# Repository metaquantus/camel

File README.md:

# Camel I2C Dual HX712 Weigh Scales Board

Camel is a board with Dual HX712 Weigh Scales ADCs controlled by a low power STM32L010F4 or STM32L031F6 MCU providing an I2C slave interface.
Power is provided by an I2C Adafruit STEMMA compatible 4-pin JST PH (2mm pitch) connector. This board will work 
with power from 3.3V to 5V, but it's better if VCC > 4V. 

It was intended to support the integrated scales mod for the Gaggia Classic Pro espresso machine provided by the Gaggiuino project. But instead of the main MCU driving the HX712s directly, sensor reading and decoding is offloaded to this board's MCU and a simple I2C interface is used instead to connect to the host MCU. This reduces the number of wires required, frees some pins in the host MCU and saves some clock cycles.

STEMMA Pinouts:
```
1 Green for SCL
2 White for SDA
3 Red for VCC+
4 Black for GND
```

The MCU drives the 2 HX712 ADCs, reads and decodes the conversions and provides the raw data to the host via I2C. 
The HX712s allow programmatic configuration of the sampling rate (10Hz or 40Hz), the amplifier's gain
factor (128 or 256) and whether to put the HX712s into power down mode consuming less than 1uA.
The device can also store configuration and calibration points in the MCU's EEPROM. Up to 4 calibration points 
are supported. 
The host is in charge of providing additional functions like scaling to weight units, tare and calibration.
It may be possible to offload scaling to the MCU, if using STM32L031F6 as it has more memory.
I2C doesn't support slave initiated transfers so the host MCU must poll the device periodically to read the data.
There will be roughly one new sensor reading available of both load cells every 100ms if 10Hz sampling rate is used. 
The internal oscillator is used in both the HX712 ADCs and the MCU so sampling rates are not very precise.
Using the lower sampling rate has lower conversion noise. The HX712 is a 24-bit ADC and data is provided in 2's complement format.
Readings could be negative depending on how the load cell is mechanically setup, bending one way of the other.
For example, in some of the integrated scales mod assembles, one cell gives positive values and 
the other negative. To get the total weight reading, the absolute values of both cells should be added.

According to STM32CubeIDE, the MCU should consume about 5mA and the HX712s about 1mA each. 

If using only one of the HX712s, it's possible power down the other, saving 1mA. This can be configured from
the host.

Programming is done via a Serial Wire Debug (SWD) connector. Both a Tag-Connect TC2030-NL and a 4-pin 2.54mm pitch header are provided for SWD.

A USART connector is provided but the STM32L010F4 has only 16Kb flash/2Kb RAM and adding code support exceeds code size limit. Some reporting
was tried but code size was very tight. This was intended for monitor and debugging during development, so it's not essential. Maybe with the
STM32L031F6 with 32KB flash/8KB RAM more monitoring and functions like standalone calibration can be added.

ESD protection diodes were added to the interface connectors.

2.54mm pitch header THT pads are used for the load cell connectors, but normally the load cells wires should be soldered directly to the pads instead of using headers or other connector.

## PCB Notes

The variable FAB\_ON\_PLACEHOLDER should be set to JLCJLCJLCJLC, WayWayWay or whatever string is specified by the Fab to position the order number.
Or removed altogether if so desired. Sometimes a fee is incurred if removed.

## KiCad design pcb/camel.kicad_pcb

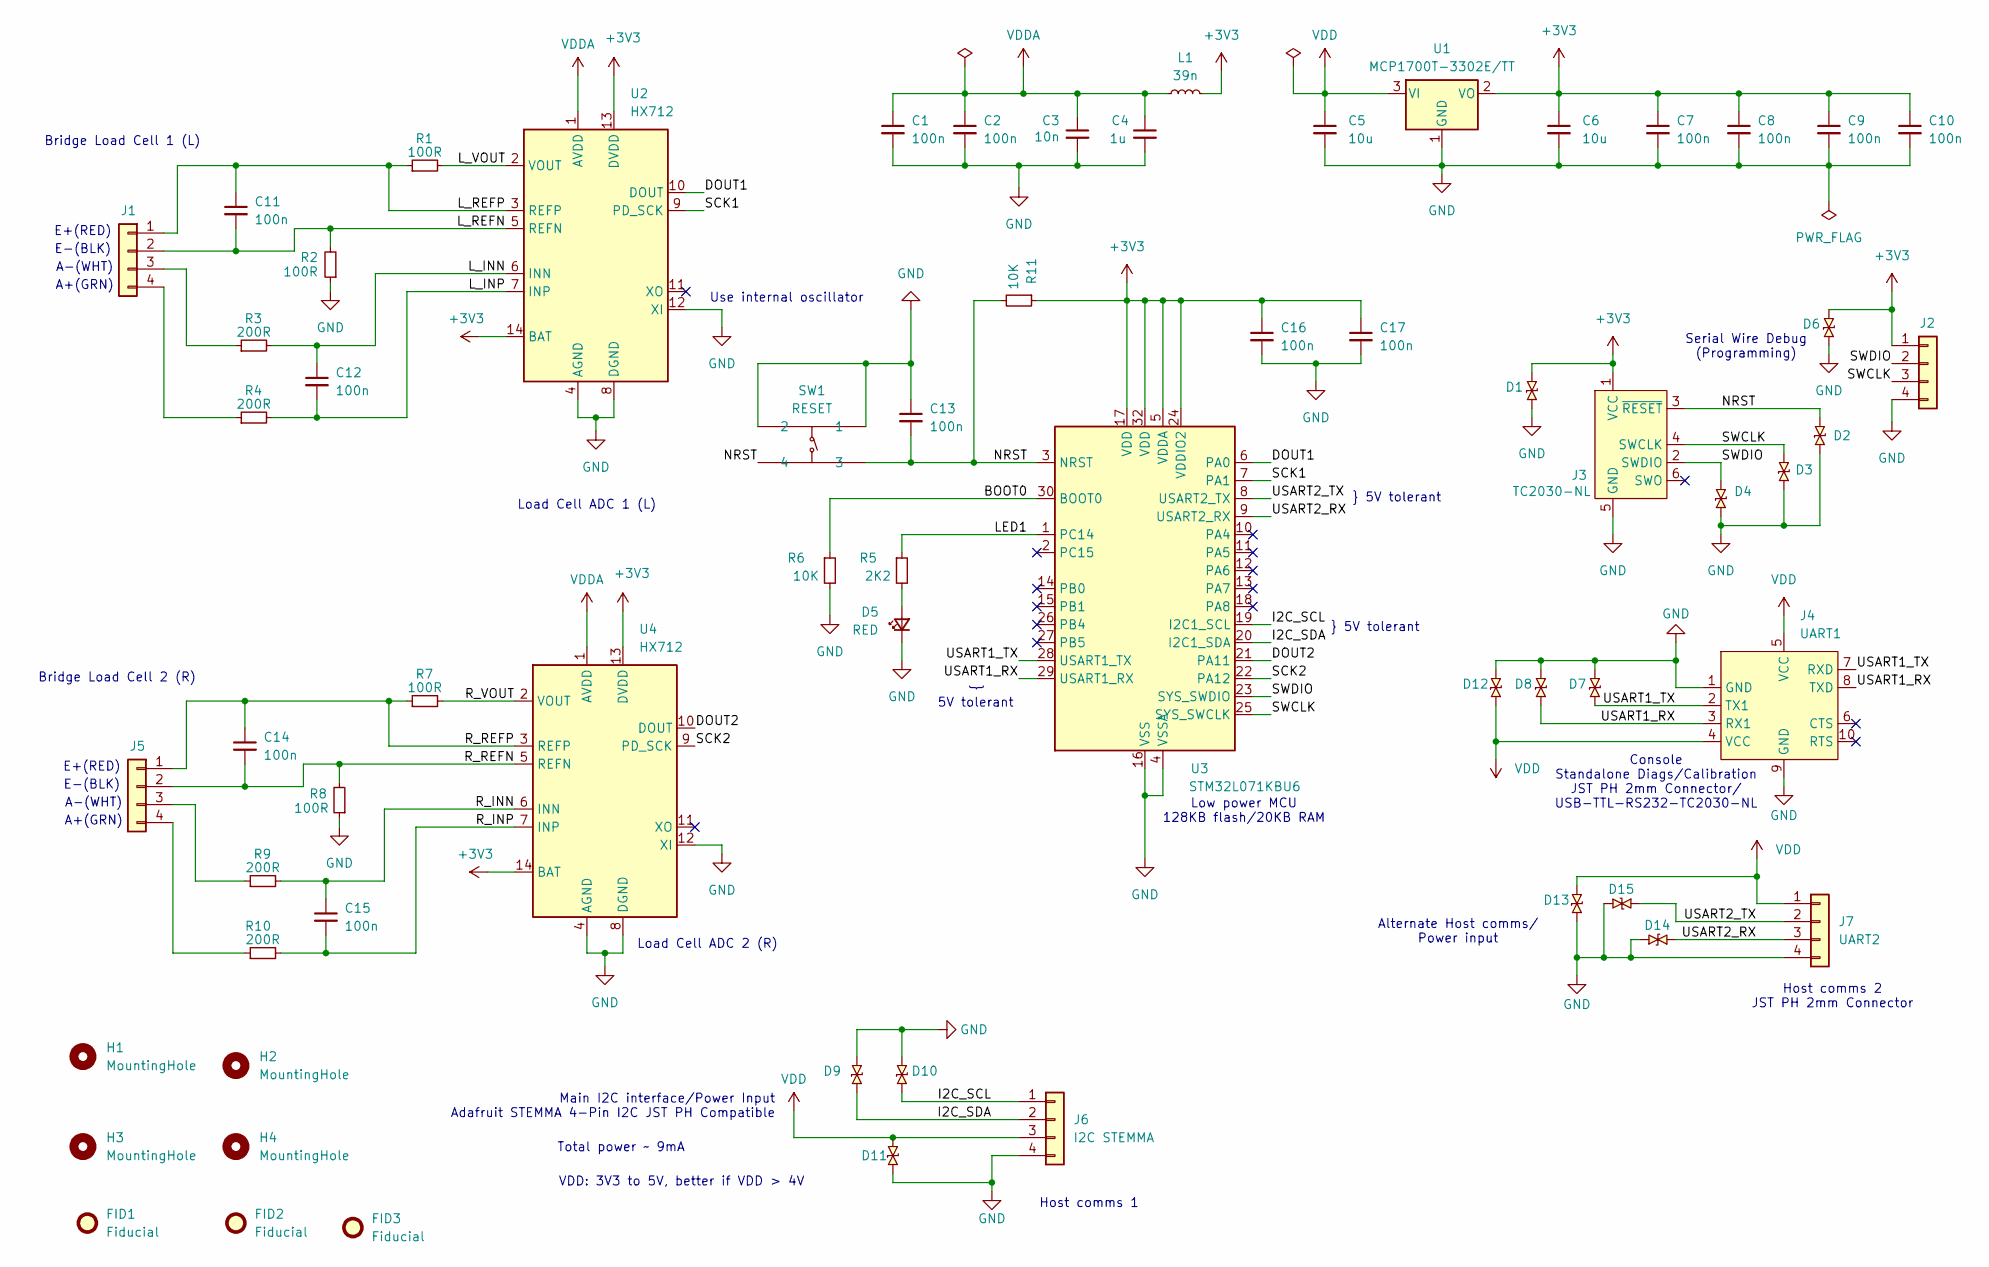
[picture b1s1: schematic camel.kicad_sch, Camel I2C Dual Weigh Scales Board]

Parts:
C1, C2, C7, C8, C9, C10, C11, C12, C13, C14, C15, C16, C17: 100n; C_0402_1005Metric; LCSC C1525
C3: 10n; C_0402_1005Metric; LCSC C15195
C4: 1u; C_0402_1005Metric; LCSC C29266
C5, C6: 10u; C_0603_1608Metric; LCSC C96446
D1, D2, D3, D4, D6, D7, D8, D9, D10, D11, D12, D13, D14, D15: RCLAMP0521P-N; X1-DFN1006-2_L1.0-W0.6-BI; LCSC C316043
D5: RED; LED_0603_1608Metric; LCSC C2286
FID1, FID2, FID3: Fiducial; Fiducial_0.5mm_Mask1mm
H1, H2, H3, H4: MountingHole; MountingHole_3.2mm_M3
J1, J2, J5: Conn_01x04; Pad_1x04_P2.54mm
J3: TC2030-NL; Tag-Connect_TC2030-IDC-NL_2x03_P1.27mm_Vertical
J4: UART1; JST_PH_S4B-PH-K_1x04_P2.00mm_Horizontal_TC-2030-IDC-NL_2x03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
J6: I2C STEMMA; JST_PH_S4B-PH-K_1x04_P2.00mm_Horizontal; LCSC C265452
J7: UART2; JST_PH_S4B-PH-K_1x04_P2.00mm_Horizontal
L1: 39n; L_1008_2520Metric; LCSC C346422
R1, R2, R7, R8: 100R; R_0402_1005Metric; LCSC C328416
R3, R4, R9, R10: 200R; R_0402_1005Metric; LCSC C413070
R5: 2K2; R_0402_1005Metric; LCSC C25879
R6, R11: 10K; R_0402_1005Metric; LCSC C317926
SW1: RESET; SW-SMD_4P-L3.0-W2.6-P1.80-LS3.5; LCSC Part C390663
U1: MCP1700T-3302E/TT; SOT-23; LCSC C39051
U2, U4: HX712; SOIC-14_3.9x8.7mm_P1.27mm; LCSC C118237
U3: STM32L071KBU6; QFN-32-1EP_5x5mm_P0.5mm_EP3.45x3.45mm; LCSC C911078

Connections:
+3V3: C6.1, C7.1, C8.1, C9.1, C10.1, C16.1, C17.1, D1.1, D6.1, J2.1, J3.1 (VCC), L1.2, R11.1, U1.2 (VO), U2.13 (DVDD), U2.14 (BAT), U3.5 (VDDA), U3.17 (VDD), U3.24 (VDDIO2), U3.32 (VDD), U4.13 (DVDD), U4.14 (BAT)
/BOOT0: R6.1, U3.30 (BOOT0)
/DOUT1: U2.10 (DOUT), U3.6 (PA0)
/DOUT2: U3.21 (PA11), U4.10 (DOUT)
/I2C_SCL: D10.2, J6.1, U3.19 (I2C1_SCL)
/I2C_SDA: D9.2, J6.2, U3.20 (I2C1_SDA)
/LED1: R5.1, U3.1 (PC14)
/L_INN: C12.1, R3.2, U2.6 (INN)
/L_INP: C12.2, R4.2, U2.7 (INP)
/L_REFN: C11.2, J1.2, R2.2, U2.5 (REFN)
/L_REFP: C11.1, J1.1, R1.1, U2.3 (REFP)
/L_VOUT: R1.2, U2.2 (VOUT)
/NRST: C13.2, D2.1, J3.3 (~RESET), R11.2, SW1.3, SW1.4, U3.3 (NRST)
/R_INN: C15.1, R9.2, U4.6 (INN)
/R_INP: C15.2, R10.2, U4.7 (INP)
/R_REFN: C14.2, J5.2, R8.2, U4.5 (REFN)
/R_REFP: C14.1, J5.1, R7.1, U4.3 (REFP)
/R_VOUT: R7.2, U4.2 (VOUT)
/SCK1: U2.9 (PD_SCK), U3.7 (PA1)
/SCK2: U3.22 (PA12), U4.9 (PD_SCK)
/SWCLK: D3.1, J2.3, J3.4 (SWCLK), U3.25 (SYS_SWCLK)
/SWDIO: D4.1, J2.2, J3.2 (SWDIO), U3.23 (SYS_SWDIO)
/USART1_RX: D8.2, J4.3 (RX1), J4.8 (TXD), U3.29 (USART1_RX)
/USART1_TX: D7.2, J4.2 (TX1), J4.7 (RXD), U3.28 (USART1_TX)
/USART2_RX: D14.2, J7.3, U3.9 (USART2_RX)
/USART2_TX: D15.2, J7.2, U3.8 (USART2_TX)
GND: C1.2, C2.2, C3.2, C4.2, C5.2, C6.2, C7.2, C8.2, C9.2, C10.2, C13.1, C16.2, C17.2, D1.2, D2.2, D3.2, D4.2, D5.1 (K), D6.2, D7.1, D8.1, D9.1, D10.1, D11.2, D12.1, D13.2, D14.1, D15.1, J2.4, J3.5 (GND), J4.1 (GND), J4.9 (GND), J6.4, J7.4, R2.1, R6.2, R8.1, SW1.1, SW1.2, U1.1 (GND), U2.4 (AGND), U2.8 (DGND), U2.12 (XI), U3.4 (VSSA), U3.16 (VSS), U3.31 (VSS), U3.33 (VSS), U4.4 (AGND), U4.8 (DGND), U4.12 (XI)
unnamed: D5.2 (A), R5.2
unnamed: J1.3, R3.1
unnamed: J1.4, R4.1
unnamed: J5.3, R9.1
unnamed: J5.4, R10.1
VDD: C5.1, D11.1, D12.2, D13.1, J4.4 (VCC), J4.5 (VCC), J6.3, J7.1, U1.3 (VI)
VDDA: C1.1, C2.1, C3.1, C4.1, L1.1, U2.1 (AVDD), U4.1 (AVDD)

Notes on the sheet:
A-(WHT)
Bridge Load Cell 2 (R)
5V tolerant
Alternate Host comms/ Power input
Load Cell ADC 2 (R)
Host comms 2 JST PH 2mm Connector
Host comms 1
VDD: 3V3 to 5V, better if VDD > 4V
Console Standalone Diags/Calibration JST PH 2mm Connector/ USB-TTL-RS232-TC2030-NL
E+(RED)
Main I2C interface/Power Input Adafruit STEMMA 4-Pin I2C JST PH Compatible
Total power ~ 9mA
A+(GRN)
Low power MCU 128KB flash/20KB RAM
E-(BLK)
Load Cell ADC 1 (L)
Serial Wire Debug (Programming)
} 5V tolerant
Use internal oscillator
Bridge Load Cell 1 (L)

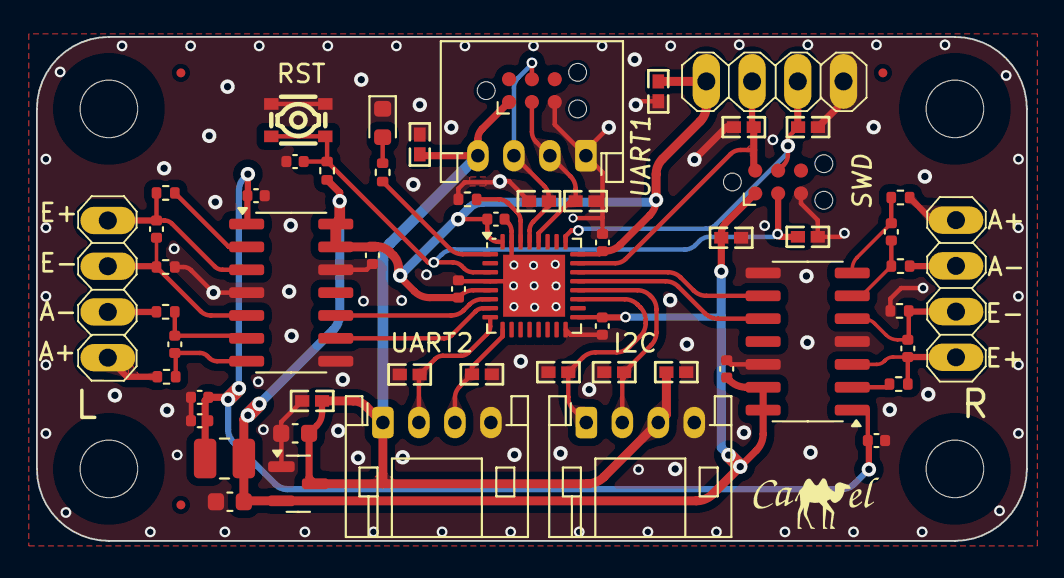
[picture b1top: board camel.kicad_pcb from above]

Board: 4 copper layers, 55.0 x 28.0 mm, 65 parts (1 on the bottom side), 34 nets.

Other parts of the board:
G3: LOGO; camel_logo_7
QR1: QR; camel_qrcode_5x5

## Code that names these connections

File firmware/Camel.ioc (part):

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Mcu.Name=STM32L071K(B-Z)Ux
Mcu.Package=UFQFPN32
Mcu.UserName=STM32L071KBUx
PA0.GPIOParameters=GPIO_Label,GPIO_ModeDefaultEXTI
PA0.GPIO_Label=DOUT1
PA0.GPIO_ModeDefaultEXTI=GPIO_MODE_IT_FALLING
PA0.Signal=GPXTI0
PA1.GPIOParameters=GPIO_Label
PA1.GPIO_Label=SCK1
PA1.Signal=GPIO_Output
PA10.Mode=I2C
PA10.Signal=I2C1_SDA
PA11.GPIOParameters=GPIO_Label,GPIO_ModeDefaultEXTI
PA11.GPIO_Label=DOUT2
PA11.GPIO_ModeDefaultEXTI=GPIO_MODE_IT_FALLING
PA11.Signal=GPXTI11
PA12.GPIOParameters=GPIO_Label
PA12.GPIO_Label=SCK2
PA12.Signal=GPIO_Output
PA13.Mode=Serial_Wire
PA13.Signal=SYS_SWDIO
PA14.Mode=Serial_Wire
PA14.Signal=SYS_SWCLK
PA2.Mode=Asynchronous
PA2.Signal=USART2_TX
PA3.Mode=Asynchronous
PA3.Signal=USART2_RX
PA9.Mode=I2C
PA9.Signal=I2C1_SCL
PB6.Mode=Asynchronous
PB6.Signal=USART1_TX
PB7.Mode=Asynchronous
PB7.Signal=USART1_RX
PC14-OSC32_IN.GPIOParameters=GPIO_Label
PC14-OSC32_IN.GPIO_Label=LED1
PC14-OSC32_IN.Signal=GPIO_Output
RCC.SYSCLKFreq_VALUE=32000000
RCC.SYSCLKSource=RCC_SYSCLKSOURCE_PLLCLK
board=custom

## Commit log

2024-10-12 Initial import
2024-10-23 first pass
2024-10-23 update docs
2024-10-27 firmware initial code
2024-10-29 completed implementation
2024-10-29 some refactoring
2024-11-08 added extra SWD connector in addition to TagConnect
2024-11-10 replaced with hx712, updated schematics and pcb
2024-11-15 PCB updates, teardrops and trace cleanup
2024-11-23 PCB refactoring, BOM updates, firmware added EEPROM storage of configuration
2024-11-28 PCBway additions
2025-07-04 updated STM32CubeMX version, updating to STM32L031F6
2025-07-07 version 3.0 update MCU and VDD on USART connector, prepare for JLCPCB
2025-07-09 device tare and calibration functions
2025-07-24 Starting to update MCU
2025-07-24 updated to PCB ver 3.0
2025-07-30 updating MCU
2025-08-30 Update to STM32L071 and FreeRTOS, first stage
